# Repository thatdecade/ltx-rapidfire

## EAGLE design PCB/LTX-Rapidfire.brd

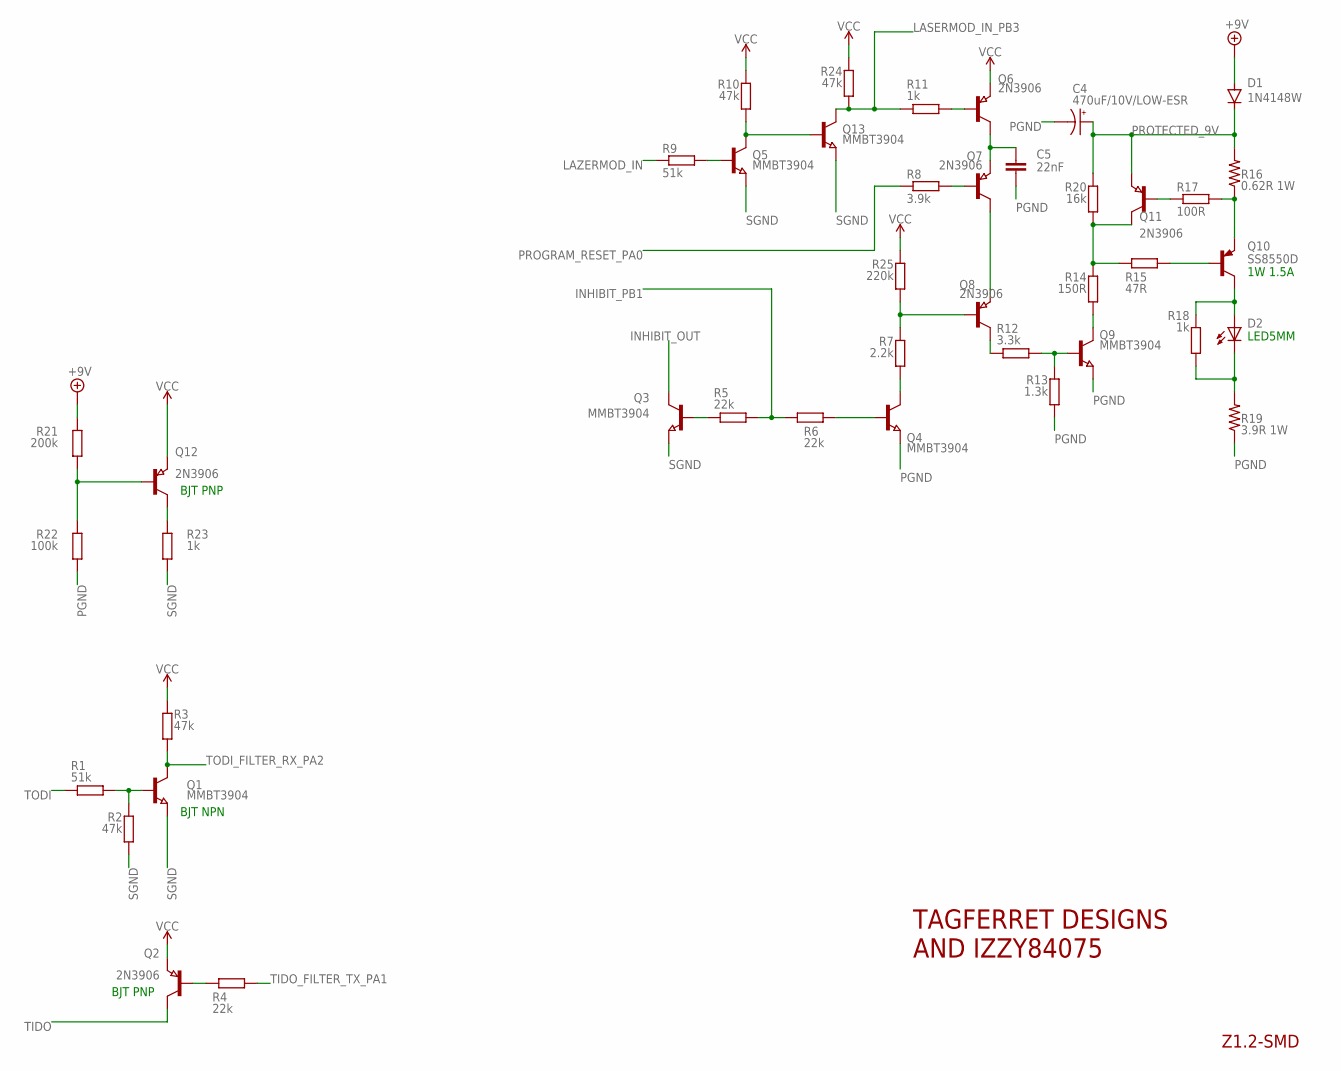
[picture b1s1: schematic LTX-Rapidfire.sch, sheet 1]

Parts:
C4: 470uF/10V/LOW-ESR; E3,5-8; LCSC C43332
C5: 22nF; C0603
D1: 1N4148W; SOD123
D2: LED5MM
Q1, Q3, Q4, Q5, Q9, Q13: MMBT3904; SOT23
Q2, Q6, Q7, Q8, Q11, Q12: 2N3906; SOT23; LCSC_PART C147294
Q10: SS8550D; TO92; LCSC_PART C118551
R1, R9: 51k; R0603
R2, R3, R10, R24: 47k; R0603
R4, R5, R6: 22k; R0603
R7: 2.2k; R0603
R8: 3.9k; R0603
R11, R18, R23: 1k; R0603
R12: 3.3k; R0603
R13: 1.3k; R0603; LCSC_PART C22767
R14: 150R; R0603
R15: 47R; R0603
R16: 0.62R 1W; R2512; LCSC_PART C705623
R17: 100R; R0603
R19: 3.9R 1W; R2512; LCSC_PART C66801
R20: 16k; R0805
R21: 200k; R0603
R22: 100k; R0603
R25: 220k; R0603

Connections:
+9V: D1.A, R21.2; also elsewhere on the board
INHIBIT_OUT: Q3.3 (C); also elsewhere on the board
INHIBIT_PB1: R5.2, R6.1; also elsewhere on the board
LASERMOD_IN_PB3: Q13.3 (C), R11.1, R24.1; also elsewhere on the board
LAZERMOD_IN: R9.1; also elsewhere on the board
unnamed: Q11.1 (B), R17.1
unnamed: Q10.3 (E), R16.1, R17.2
unnamed: Q11.3 (C), R14.2, R15.1, R20.1
unnamed: Q10.2 (B), R15.2
unnamed: Q9.3 (C), R14.1
unnamed: D2.K (C), R18.1, R19.2
unnamed: D2.A, Q10.1 (C), R18.2
unnamed: Q9.1 (B), R12.2, R13.2
unnamed: Q8.3 (C), R12.1
unnamed: Q7.3 (C), Q8.2 (E)
unnamed: Q8.1 (B), R7.2, R25.1
unnamed: Q7.1 (B), R8.2
unnamed: Q4.3 (C), R7.1
unnamed: C5.1, Q6.3 (C), Q7.2 (E)
unnamed: Q4.1 (B), R6.2
unnamed: Q12.3 (C), R23.2
unnamed: Q3.1 (B), R5.1
unnamed: Q6.1 (B), R11.2
unnamed: Q12.1 (B), R21.1, R22.2
unnamed: Q5.3 (C), Q13.1 (B), R10.1
unnamed: Q5.1 (B), R9.2
unnamed: Q1.1 (B), R1.2, R2.2
unnamed: Q2.1 (B), R4.1
PGND: C4.-, C5.2, Q4.2 (E), Q9.2 (E), R13.1, R19.1, R22.1; also elsewhere on the board
PROGRAM_RESET_PA0: R8.1; also elsewhere on the board
PROTECTED_9V: C4.+, D1.C, Q11.2 (E), R16.2, R20.2
SGND: Q1.2 (E), Q3.2 (E), Q5.2 (E), Q13.2 (E), R2.1, R23.1; also elsewhere on the board
TIDO: Q2.3 (C); also elsewhere on the board
TIDO_FILTER_TX_PA1: R4.2; also elsewhere on the board
TODI: R1.1; also elsewhere on the board
TODI_FILTER_RX_PA2: Q1.3 (C), R3.1; also elsewhere on the board
VCC: Q2.2 (E), Q6.2 (E), Q12.2 (E), R3.2, R10.2, R24.2, R25.2; also elsewhere on the board

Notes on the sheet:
TAGFERRET DESIGNS AND IZZY84075
Z1.2-SMD
BJT PNP
BJT NPN
LED5MM
1W 1.5A

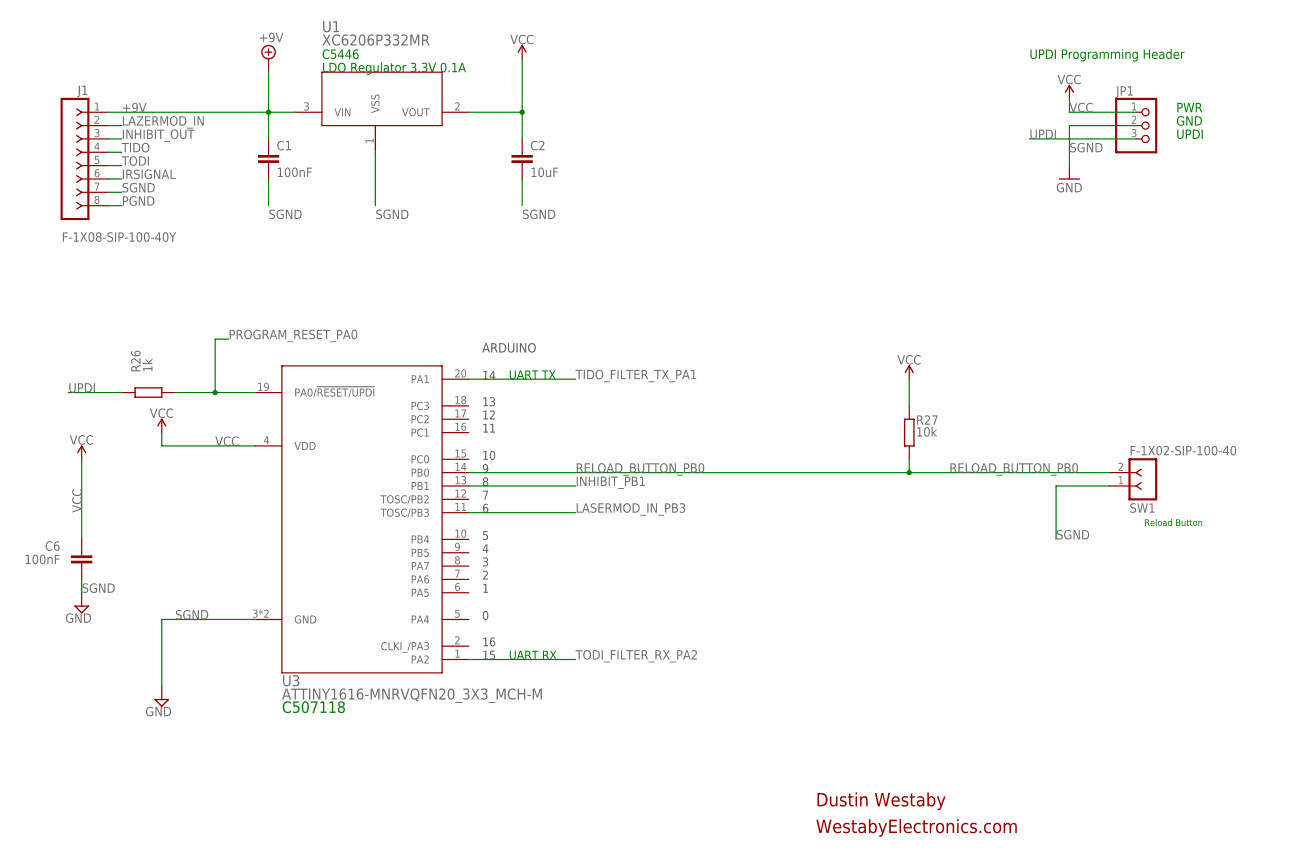
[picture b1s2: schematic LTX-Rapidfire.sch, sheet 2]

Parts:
C1, C6: 100nF; C0603
C2: 10uF; C0603
J1: F-1X08-SIP-100-40Y; SIP-100-08-40Y
JP1: PINHD-1X3; 1X03
R26: 1k; R0603
R27: 10k; R0603
SW1: F-1X02-SIP-100-40; SIP-100-02-40
U1: XC6206P332MR; SOT-23_TOR; LCSC_PART C5446
U3: ATTINY1616-MNRVQFN20_3X3_MCH-M; VQFN20_3X3_MCH-M

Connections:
+9V: C1.1, J1.1, U1.3 (VIN); also elsewhere on the board
INHIBIT_OUT: J1.3; also elsewhere on the board
INHIBIT_PB1: U3.13 (PB1); also elsewhere on the board
IRSIGNAL: J1.6
LASERMOD_IN_PB3: U3.11 (TOSC/PB3); also elsewhere on the board
LAZERMOD_IN: J1.2; also elsewhere on the board
PGND: J1.8; also elsewhere on the board
PROGRAM_RESET_PA0: R26.1, U3.19 (PA0/!RESET/UPDI); also elsewhere on the board
RELOAD_BUTTON_PB0: R27.2, SW1.2, U3.14 (PB0)
SGND: C1.2, C2.2, C6.2, J1.7, JP1.2, SW1.1, U1.1 (VSS), U3.3 (GND), U3.21 (GND); also elsewhere on the board
TIDO: J1.4; also elsewhere on the board
TIDO_FILTER_TX_PA1: U3.20 (PA1); also elsewhere on the board
TODI: J1.5; also elsewhere on the board
TODI_FILTER_RX_PA2: U3.1 (PA2); also elsewhere on the board
UPDI: JP1.3, R26.2
VCC: C2.1, C6.1, JP1.1, R27.1, U1.2 (VOUT), U3.4 (VDD); also elsewhere on the board

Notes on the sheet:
UART TX
UART RX
C507118
14 13 12 11
10 9 8 7 6
5 4 3 2 1
0 16 15
ARDUINO
Dustin Westaby
WestabyElectronics.com
UPDI Programming Header
Reload Button
LDO Regulator 3.3V 0.1A
C5446
PWR
GND
UPDI

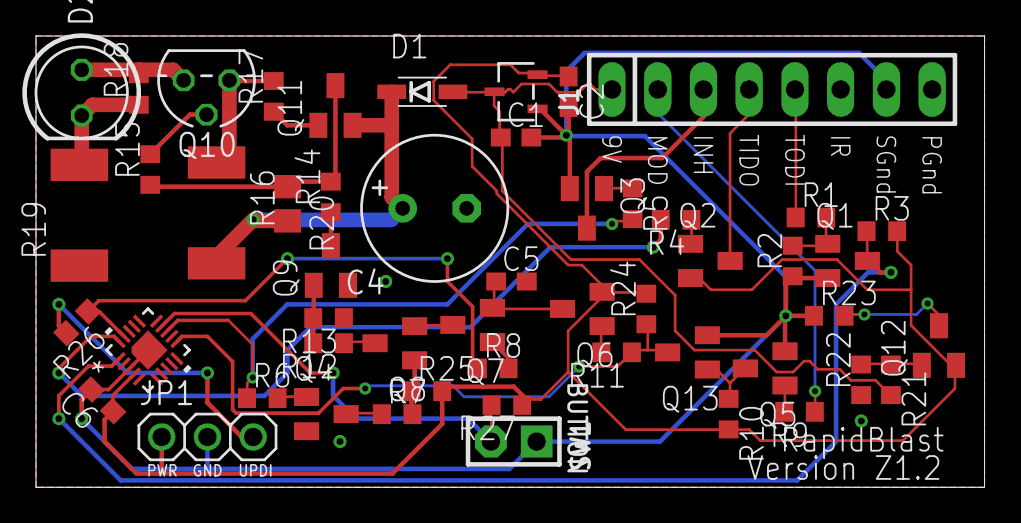
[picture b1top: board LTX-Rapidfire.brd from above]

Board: 2 copper layers, 52.7 x 25.1 mm, 52 parts (0 on the bottom side), 39 nets.

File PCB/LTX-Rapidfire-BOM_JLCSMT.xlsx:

Comment | Designator | Footprint | JLCPCB Part #（optional）
100nF | C1 | C0603 | C14663
10uF | C2 | C0603 | C96446
470uF/10V/LOW-ESR | C4 | E3,5-8 | C43332
22nF | C5 | C0603 | C21122
100nF | C6 | C0603 | C14663
1N4148W | D1 | SOD123 | C81598
 | D2 | LED5MM
F-1X08-SIP-100-40Y | J1 | SIP-100-08-40Y
 | JP1 | 1X03
MMBT3904 | Q1 | SOT23 | C20526
2N3906 | Q2 | SOT23 | C147294
MMBT3904 | Q3 | SOT23 | C20526
MMBT3904 | Q4 | SOT23 | C20526
MMBT3904 | Q5 | SOT23 | C20526
2N3906 | Q6 | SOT23 | C147294
2N3906 | Q7 | SOT23 | C147294
2N3906 | Q8 | SOT23 | C147294
MMBT3904 | Q9 | SOT23 | C20526
SS8550D | Q10 | TO92 | C118551
2N3906 | Q11 | SOT23 | C147294
2N3906 | Q12 | SOT23 | C147294
MMBT3904 | Q13 | SOT23 | C20526
51k | R1 | R0603 | C23196
47k | R2 | R0603 | C25819
47k | R3 | R0603 | C25819
22k | R4 | R0603 | C31850
22k | R5 | R0603 | C31850
22k | R6 | R0603 | C31850
2.2k | R7 | R0603 | C4190
3.9k | R8 | R0603 | C23018
51k | R9 | R0603 | C23196
47k | R10 | R0603 | C25819
1k | R11 | R0603 | C21190
3.3k | R12 | R0603 | C22978
1.3k | R13 | R0603 | C22767
150R | R14 | R0603 | C22808
47R | R15 | R0603 | C23182
0.62R 1W | R16 | R2512 | C705623
100R | R17 | R0603 | C22775
1k | R18 | R0603 | C21190
3.9R 1W | R19 | R2512 | C66801
16k | R20 | R0805 | C17490
200k | R21 | R0603 | C25811
100k | R22 | R0603 | C25803
1k | R23 | R0603 | C21190
47k | R24 | R0603 | C25819
220k | R25 | R0603 | C22961
10k | R27 | R0603 | C25804
1K | R28 | R0603 | C21190
F-1X02-SIP-100-40 | SW1 | SIP-100-02-40
XC6206P332MR | U1 | SOT-23_TOR | C5446
ATTINY1616-MNRVQFN20_3X3_MCH-M | U3 | VQFN20_3X3_MCH-M | C507118

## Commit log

2022-10-05 Labeled part numbers in schematic. Prep for SMD-ification
2022-10-05 Swapped basics to SMD
2022-10-07 Part lists and gerbers for JLC
2022-10-10 Swapped chip and routed pcb
2022-10-10 Updated gerbers, com, and placement

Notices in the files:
parts and their libraries:
con-headers-jp: Copyright (C) 2008, Bob Starr
COPYRIGHT: Copyright (C) 2022 Ultra Librarian. All rights reserved.
SparkFun-PowerSymbols: Licensing: Creative Commons ShareAlike 4.0 International - https://creativecommons.org/licenses/by-sa/4.0
